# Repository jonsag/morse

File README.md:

# morse

Morse decoding and training gadgets

## Sections

This project will (probably) consist of two parts:  

* A CW paddle keyer  
* A morse decoder  

I have no real intention with this, other than that I think it could be fun testing these things out.  

### Keyer

A keyer based on the [nanoKeyer](https://nanokeyer.wordpress.com/) by Oscar, DJ0MY.  
NanoKeyer is built on the [K3NG Arduino CW Keyer](https://github.com/k3ng/k3ng_cw_keyer) open source project by [Anthony Good](https://github.com/k3ng).  
More documentation can be found at [github](https://github.com/ra0sms/nanokeyer).  

There's also the keyer, [Iambic Keyer Using Microcontroller](https://www.instructables.com/Iambic-Keyer-Using-Microcontroller/) by [fredlam](https://www.instructables.com/member/fredlam/).  
This uses the [PIC12F675](https://www.microchip.com/en-us/product/pic12f675), and perhaps I will delve into this approach later on, but for now I will stick to Oscar's design.  

### Decoder

A decoder based on [Morse Code Iambic Trainer and Decoder](https://www.instructables.com/Morse-Code-Iambic-Trainer-and-Decoder/) by [scd](https://www.instructables.com/member/scd/).  

## nanoKeyer build

If you don't want to print the entire casing, Oscar recommend these parts from [reichelt](https://www.reichelt.com)

* [KOH-0100, Profile housing half-shell, 100 x 6.73 mm, individually shrink-w](https://www.reichelt.com/se/en/shop/product/profile_housing_half-shell_100_x_6_73_mm_individually_shrink-w-58238?country=se&CCTYPE=private&LANGUAGE=en)  
* [KOH-4100, Profile housing half-shell, 100 x 32.1 mm, individually shrink-w](https://www.reichelt.com/se/en/shop/product/profile_housing_half-shell_100_x_32_1_mm_individually_shrink-w-58241)  
* [DPL 1-2, Cover set for half-shell profiles, KOH 1 + 2 packaged sets, 105](https://www.reichelt.com/se/en/shop/product/cover_set_for_half-shell_profiles_koh_1_2_packaged_sets_105-58257)  
* KNOPF 17-6 A, which is an aluminium knob for the potentiometer, but I couldn't find that at reichelt.  

If you instead want to print the faceplates fitting the casing above, there are stl's for [download at thingiverse](https://www.thingiverse.com/thing:4552149), designed by [Kaan, DL8GE](https://www.thingiverse.com/DL8GE).  

## Decoder build

Print the [casing found at thingiverse](https://www.thingiverse.com/thing:4875668).  

## Need a key?

The excellent twin paddle CW key by [EA7HVO](https://www.thingiverse.com/EA7HVO) can be downloaded from [thingiverse](https://www.thingiverse.com/thing:4586197).  4

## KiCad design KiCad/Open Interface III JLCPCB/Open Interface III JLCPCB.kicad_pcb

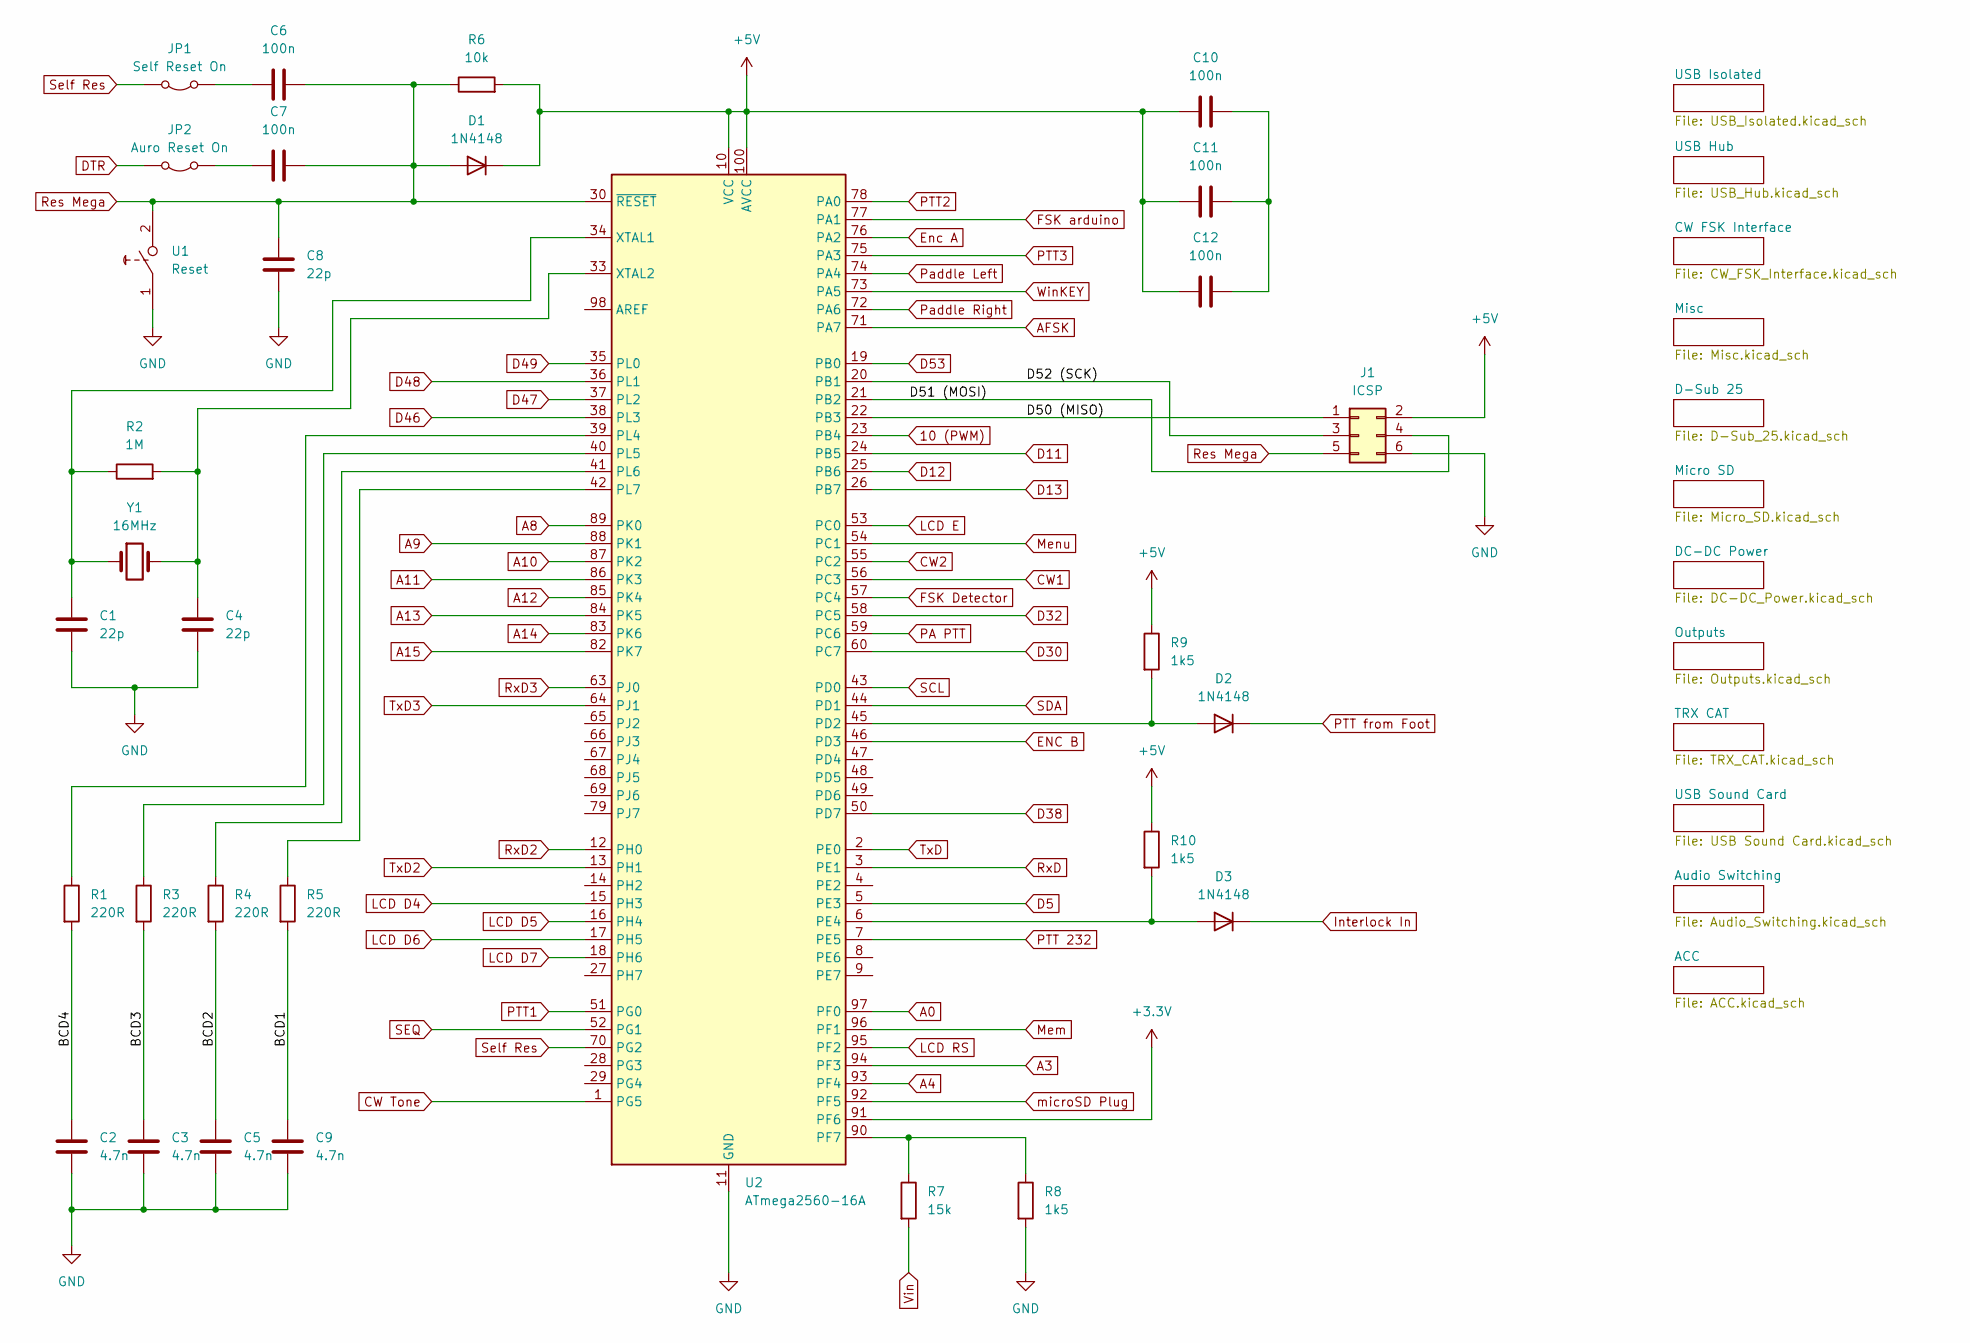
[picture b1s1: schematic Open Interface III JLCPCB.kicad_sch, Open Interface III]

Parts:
C1, C4, C8: 22p; C_0201_0603Metric; MPN C1653
C2, C3, C5, C9: 4.7n; C_0201_0603Metric; MPN C1621
C6, C7, C10, C11, C12: 100n; C_0201_0603Metric; MPN C1590
D1, D2, D3: 1N4148; D_SOD-523
J1: ICSP; 2x3_ISP_header
JP1: Self Reset On; PinHeader_1x02_P2.54mm_Vertical
JP2: Auro Reset On; PinHeader_1x02_P2.54mm_Vertical
R1, R3, R4, R5: 220R; R_0201_0603Metric; MPN C1226
R2: 1M; R_0201_0603Metric; MPN C22935
R6: 10k; R_0201_0603Metric; MPN C15401
R7: 15k; R_0201_0603Metric; MPN C22809
R8, R9, R10: 1k5; R_0201_0603Metric; MPN C22843
U1: Reset; 2-pin JST Switch
U2: ATmega2560-16A; TQFP-100_14x14mm_P0.5mm; MPN C22460
Y1: 16MHz; Crystal_SMD_HC49-SD; MPN C5346052

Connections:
10 (PWM): U2.23 (PB4); also elsewhere on the board
+3.3V: U2.91 (PF6); also elsewhere on the board
+5V: C10.1, C11.1, C12.1, D1.1 (K), J1.2, R6.2, R9.1, R10.1, U2.10 (VCC), U2.31 (VCC), U2.61 (VCC), U2.80 (VCC), U2.100 (AVCC); also elsewhere on the board
/BCD1: C9.1, R5.2
/BCD2: C5.1, R4.2
/BCD3: C3.1, R3.2
/BCD4: C2.1, R1.2
/D50 (MISO): J1.1, U2.22 (PB3)
/D51 (MOSI): J1.4, U2.21 (PB2)
/D52 (SCK): J1.3, U2.20 (PB1)
A0: U2.97 (PF0)
A3: U2.94 (PF3); also elsewhere on the board
A4: U2.93 (PF4); also elsewhere on the board
A8: U2.89 (PK0); also elsewhere on the board
A9: U2.88 (PK1); also elsewhere on the board
A10: U2.87 (PK2)
A11: U2.86 (PK3); also elsewhere on the board
A12: U2.85 (PK4)
A13: U2.84 (PK5)
A14: U2.83 (PK6)
A15: U2.82 (PK7)
AFSK: U2.71 (PA7); also elsewhere on the board
AGNDC: C1.2, C2.2, C3.2, C4.2, C5.2, C8.2, C9.2, J1.6, R8.2, U1.1 (Com), U2.11 (GND), U2.32 (GND), U2.62 (GND), U2.81 (GND), U2.99 (GND); also elsewhere on the board
CW1: U2.56 (PC3); also elsewhere on the board
CW2: U2.55 (PC2); also elsewhere on the board
CW Tone: U2.1 (PG5)
D5: U2.5 (PE3); also elsewhere on the board
D11: U2.24 (PB5); also elsewhere on the board
D12: U2.25 (PB6); also elsewhere on the board
D13: U2.26 (PB7); also elsewhere on the board
D30: U2.60 (PC7); also elsewhere on the board
D32: U2.58 (PC5); also elsewhere on the board
D38: U2.50 (PD7); also elsewhere on the board
D46: U2.38 (PL3); also elsewhere on the board
D47: U2.37 (PL2); also elsewhere on the board
D48: U2.36 (PL1)
D49: U2.35 (PL0)
D53: U2.19 (PB0); also elsewhere on the board
DTR: JP2.2 (B); also elsewhere on the board
ENC B: U2.46 (PD3)
Enc A: U2.76 (PA2); also elsewhere on the board
FSK Detector: U2.57 (PC4)
FSK arduino: U2.77 (PA1)
Interlock In: D3.1 (K); also elsewhere on the board
LCD D4: U2.15 (PH3); also elsewhere on the board
LCD D5: U2.16 (PH4); also elsewhere on the board
LCD D6: U2.17 (PH5); also elsewhere on the board
LCD D7: U2.18 (PH6)
LCD E: U2.53 (PC0); also elsewhere on the board
LCD RS: U2.95 (PF2); also elsewhere on the board
Mem: U2.96 (PF1)
Menu: U2.54 (PC1); also elsewhere on the board
unnamed: C10.2, C11.2, C12.2
unnamed: D2.2 (A), R9.2, U2.45 (PD2)
unnamed: D3.2 (A), R10.2, U2.6 (PE4)
unnamed: C6.1, JP1.1 (A)
unnamed: C7.1, JP2.1 (A)
unnamed: R7.1, R8.1, U2.90 (PF7)
unnamed: R1.1, U2.39 (PL4)
unnamed: R3.1, U2.40 (PL5)
unnamed: R4.1, U2.41 (PL6)
unnamed: R5.1, U2.42 (PL7)
unnamed: C1.1, R2.1, U2.34 (XTAL1), Y1.1
unnamed: C4.1, R2.2, U2.33 (XTAL2), Y1.2
PA PTT: U2.59 (PC6); also elsewhere on the board
PTT1: U2.51 (PG0); also elsewhere on the board
PTT2: U2.78 (PA0); also elsewhere on the board
PTT3: U2.75 (PA3); also elsewhere on the board
PTT 232: U2.7 (PE5); also elsewhere on the board
PTT from Foot: D2.1 (K); also elsewhere on the board
Paddle Left: U2.74 (PA4); also elsewhere on the board
Paddle Right: U2.72 (PA6); also elsewhere on the board
Res Mega: C6.2, C7.2, C8.1, D1.2 (A), J1.5, R6.1, U1.2 (NO), U2.30 (~RESET)
RxD: U2.3 (PE1); also elsewhere on the board
RxD2: U2.12 (PH0); also elsewhere on the board
RxD3: U2.63 (PJ0); also elsewhere on the board
SCL: U2.43 (PD0); also elsewhere on the board
SDA: U2.44 (PD1); also elsewhere on the board
SEQ: U2.52 (PG1); also elsewhere on the board
Self Res: JP1.2 (B), U2.70 (PG2)
TxD: U2.2 (PE0); also elsewhere on the board
TxD2: U2.13 (PH1); also elsewhere on the board
TxD3: U2.64 (PJ1); also elsewhere on the board
Vin: R7.2; also elsewhere on the board
WinKEY: U2.73 (PA5); also elsewhere on the board
microSD Plug: U2.92 (PF5); also elsewhere on the board

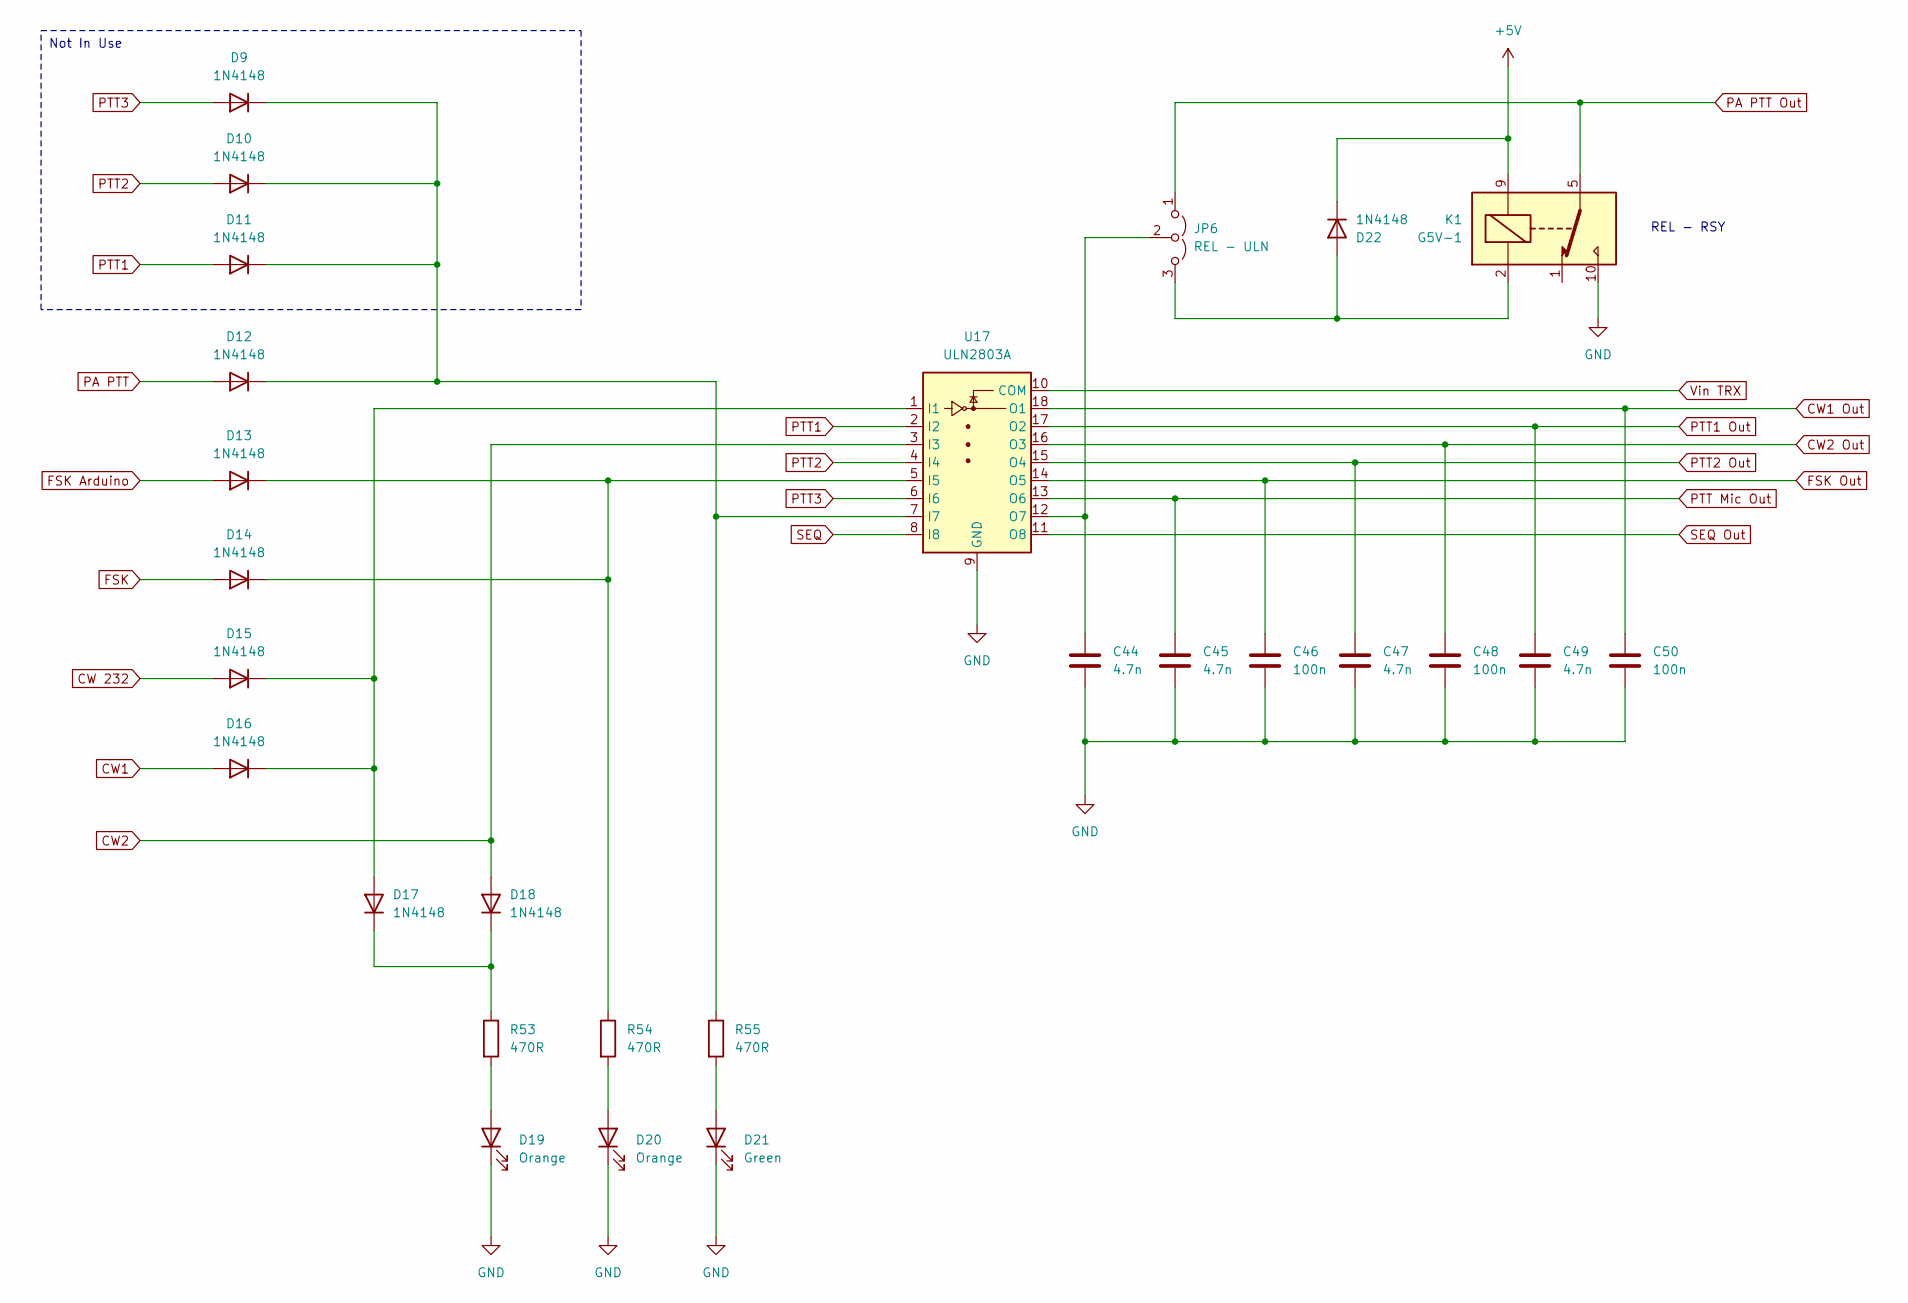
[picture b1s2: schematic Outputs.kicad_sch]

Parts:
C44, C45, C47, C49: 4.7n; C_0201_0603Metric; MPN C1621
C46, C48, C50: 100n; C_0201_0603Metric; MPN C1590
D9, D10, D11, D12, D13, D14, D15, D16, D17, D18, D22: 1N4148; D_SOD-523
D19, D20: Orange; 2-pin JST LED
D21: Green; 2-pin JST LED
JP6: REL - ULN; Jumper_1x03_P2.54mm_large
K1: G5V-1; Relay_SPDT_Omron_G5V-1
R53, R54, R55: 470R; R_0201_0603Metric; MPN C23179
U17: ULN2803A; SOIC-18W_7.5x11.6mm_P1.27mm; MPN C181731

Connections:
+5V: D22.1 (K), K1.9; also elsewhere on the board
AGNDC: C44.2, C45.2, C46.2, C47.2, C48.2, C49.2, C50.2, D19.1 (K), D20.1 (K), D21.1 (K), K1.10, U17.9 (GND); also elsewhere on the board
CW1: D16.2 (A); also elsewhere on the board
CW1 Out: C50.1, U17.18 (O1); also elsewhere on the board
CW2: D18.2 (A), U17.3 (I3); also elsewhere on the board
CW2 Out: C48.1, U17.16 (O3); also elsewhere on the board
CW 232: D15.2 (A); also elsewhere on the board
FSK: D14.2 (A); also elsewhere on the board
FSK Arduino: D13.2 (A)
FSK Out: C46.1, U17.14 (O5); also elsewhere on the board
unnamed: D9.1 (K), D10.1 (K), D11.1 (K), D12.1 (K), R55.1, U17.7 (I7)
unnamed: D13.1 (K), D14.1 (K), R54.1, U17.5 (I5)
unnamed: D15.1 (K), D16.1 (K), D17.2 (A), U17.1 (I1)
unnamed: D17.1 (K), D18.1 (K), R53.1
unnamed: D19.2 (A), R53.2
unnamed: D20.2 (A), R54.2
unnamed: D21.2 (A), R55.2
unnamed: D22.2 (A), JP6.3 (B), K1.2
unnamed: C44.1, JP6.2 (C), U17.12 (O7)
PA PTT: D12.2 (A); also elsewhere on the board
PA PTT Out: JP6.1 (A), K1.5, K1.6; also elsewhere on the board
PTT1: D11.2 (A), U17.2 (I2); also elsewhere on the board
PTT1 Out: C49.1, U17.17 (O2); also elsewhere on the board
PTT2: D10.2 (A), U17.4 (I4); also elsewhere on the board
PTT2 Out: C47.1, U17.15 (O4); also elsewhere on the board
PTT3: D9.2 (A), U17.6 (I6); also elsewhere on the board
PTT Mic Out: C45.1, U17.13 (O6); also elsewhere on the board
SEQ: U17.8 (I8); also elsewhere on the board
SEQ Out: U17.11 (O8); also elsewhere on the board
Vin TRX: U17.10 (COM); also elsewhere on the board

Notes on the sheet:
Not In Use
REL - RSY

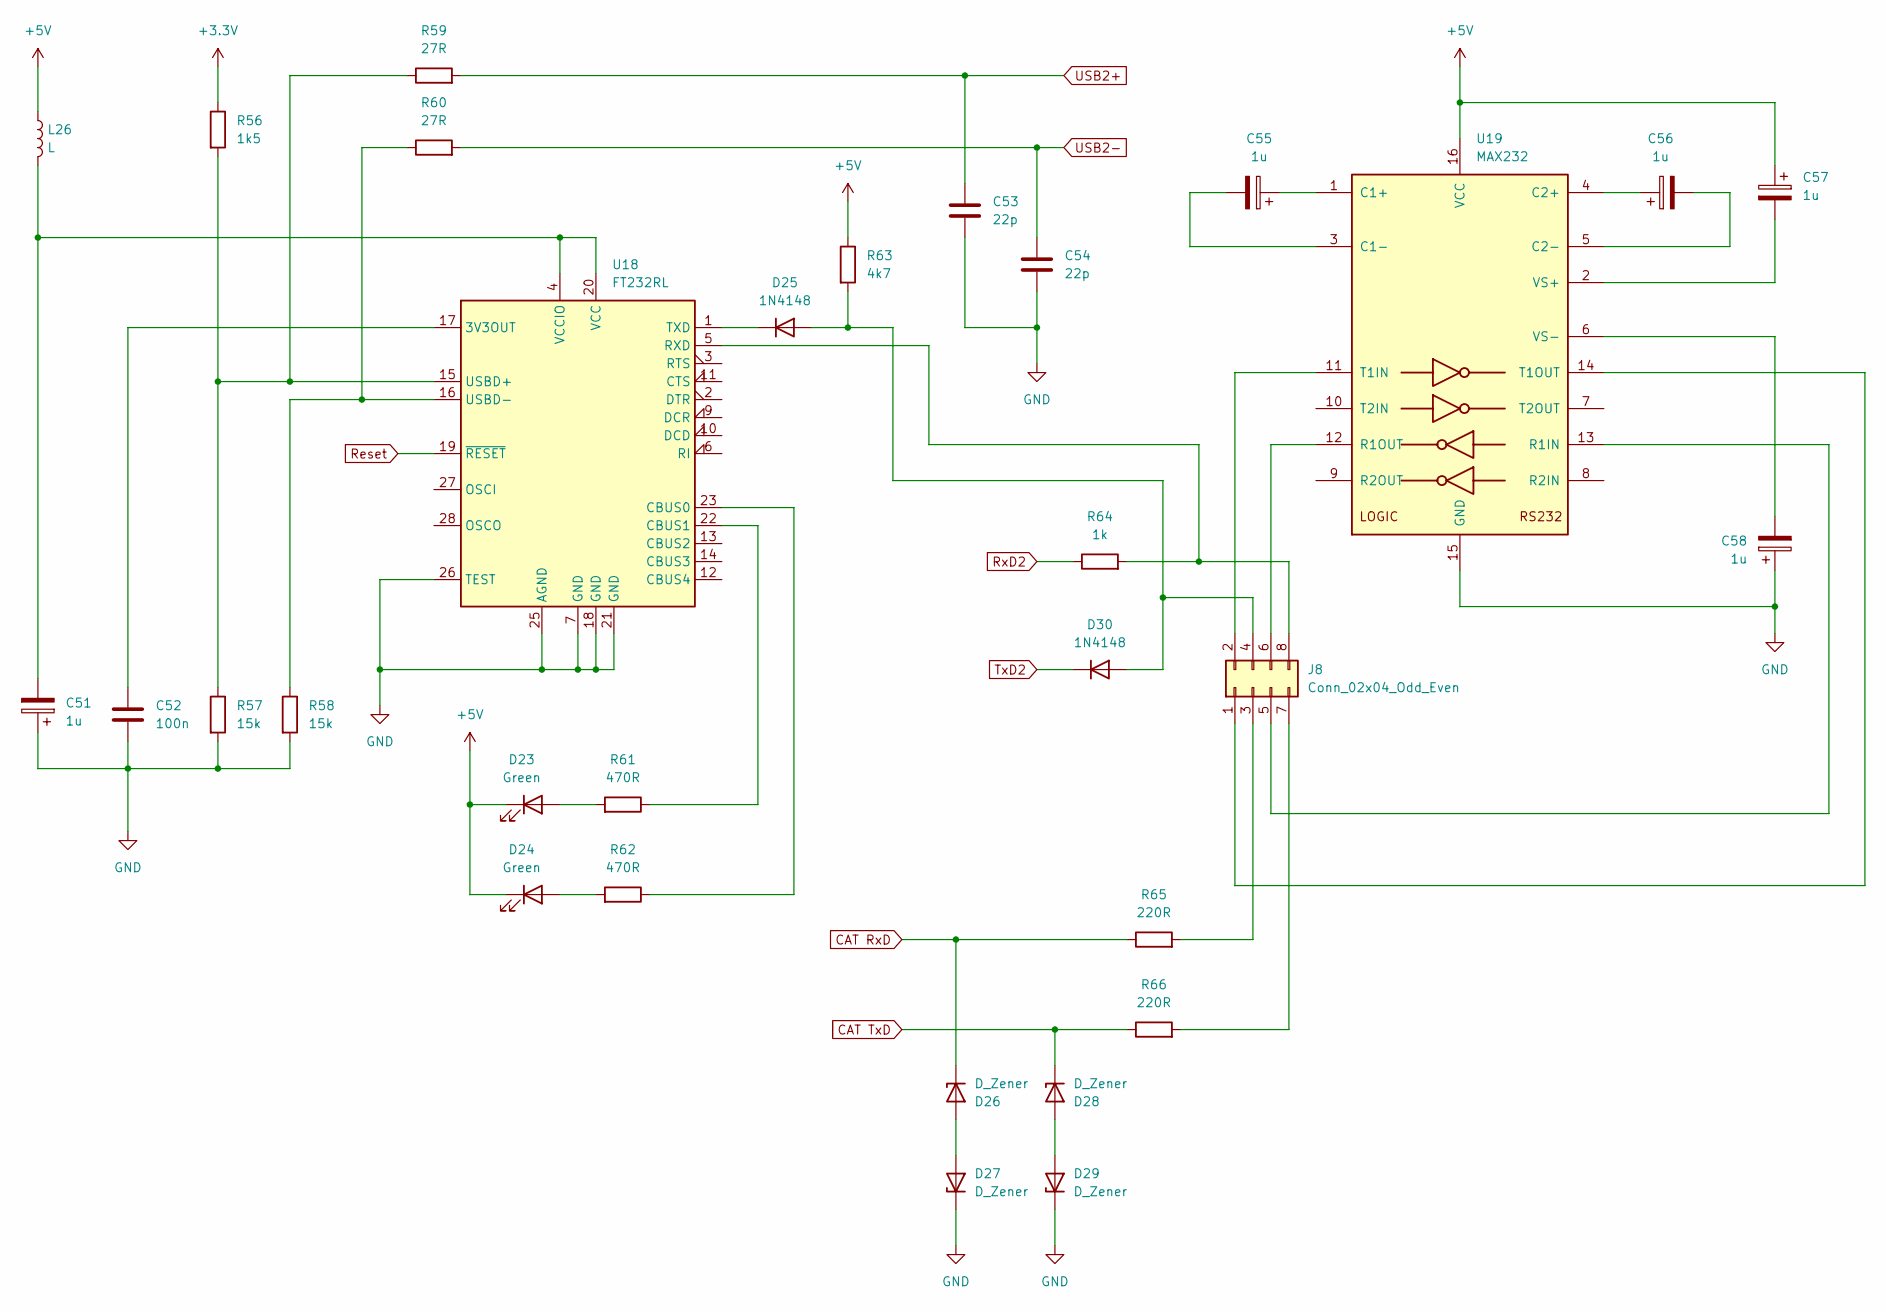
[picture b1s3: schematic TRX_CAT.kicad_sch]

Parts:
C51, C55, C56, C57, C58: 1u; CP_Elec_4x5.4; MPN C3348
C52: 100n; C_0201_0603Metric; MPN C1590
C53, C54: 22p; C_0201_0603Metric; MPN C1653
D23, D24: Green; 2-pin JST LED
D25, D30: 1N4148; D_SOD-523
D26, D27, D28, D29: D_Zener; SOT-23_Handsoldering
J8: Conn_02x04_Odd_Even; PinHeader_2x04_P2.54mm_Vertical
L26: L; L_1206_3216Metric_Pad1.22x1.90mm_HandSolder
R56: 1k5; R_0201_0603Metric; MPN C22843
R57, R58: 15k; R_0201_0603Metric; MPN C22809
R59, R60: 27R; R_0201_0603Metric; MPN C25190
R61, R62: 470R; R_0201_0603Metric; MPN C23179
R63: 4k7; R_0201_0603Metric; MPN C23162
R64: 1k; R_0201_0603Metric; MPN C14676
R65, R66: 220R; R_0201_0603Metric; MPN C1226
U18: FT232RL; SSOP-28_5.3x10.2mm_P0.65mm
U19: MAX232; SOP-16_3.9x9.9mm_P1.27mm; MPN C5342103

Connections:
+3.3V: R56.1; also elsewhere on the board
+5V: C57.1, D23.1 (K), D24.1 (K), L26.1, R63.1, U19.16 (VCC); also elsewhere on the board
AGNDC: C51.1, C52.2, C53.2, C54.2, C58.1, D27.1 (K), D29.1 (K), R57.2, R58.2, U18.7 (GND), U18.18 (GND), U18.21 (GND), U18.25 (AGND), U18.26 (TEST), U19.15 (GND); also elsewhere on the board
CAT RxD: D26.1 (K), R65.1; also elsewhere on the board
CAT TxD: D28.1 (K), R66.1; also elsewhere on the board
DTR: U18.19 (~RESET); also elsewhere on the board
unnamed: D23.2 (A), R61.2
unnamed: D24.2 (A), R62.2
unnamed: D25.2 (A), D30.2 (A), J8.4, R63.2
unnamed: D25.1 (K), U18.1 (TXD)
unnamed: D26.2 (A), D27.2 (A)
unnamed: D28.2 (A), D29.2 (A)
unnamed: J8.1, U19.14 (T1OUT)
unnamed: J8.2, U19.11 (T1IN)
unnamed: J8.3, R65.2
unnamed: J8.5, U19.13 (R1IN)
unnamed: J8.6, U19.12 (R1OUT)
unnamed: J8.7, R66.2
unnamed: J8.8, R64.2, U18.5 (RXD)
unnamed: C52.1, U18.17 (3V3OUT)
unnamed: R62.1, U18.23 (CBUS0)
unnamed: R61.1, U18.22 (CBUS1)
unnamed: R56.2, R57.1, R59.1, U18.15 (USBD+)
unnamed: R58.1, R60.1, U18.16 (USBD-)
unnamed: C51.2, L26.2, U18.4 (VCCIO), U18.20 (VCC)
unnamed: C55.1, U19.1 (C1+)
unnamed: C55.2, U19.3 (C1-)
unnamed: C56.1, U19.4 (C2+)
unnamed: C56.2, U19.5 (C2-)
unnamed: C57.2, U19.2 (VS+)
unnamed: C58.2, U19.6 (VS-)
RxD2: R64.1; also elsewhere on the board
TxD2: D30.1 (K); also elsewhere on the board
USB2+: C53.1, R59.2; also elsewhere on the board
USB2-: C54.1, R60.2; also elsewhere on the board

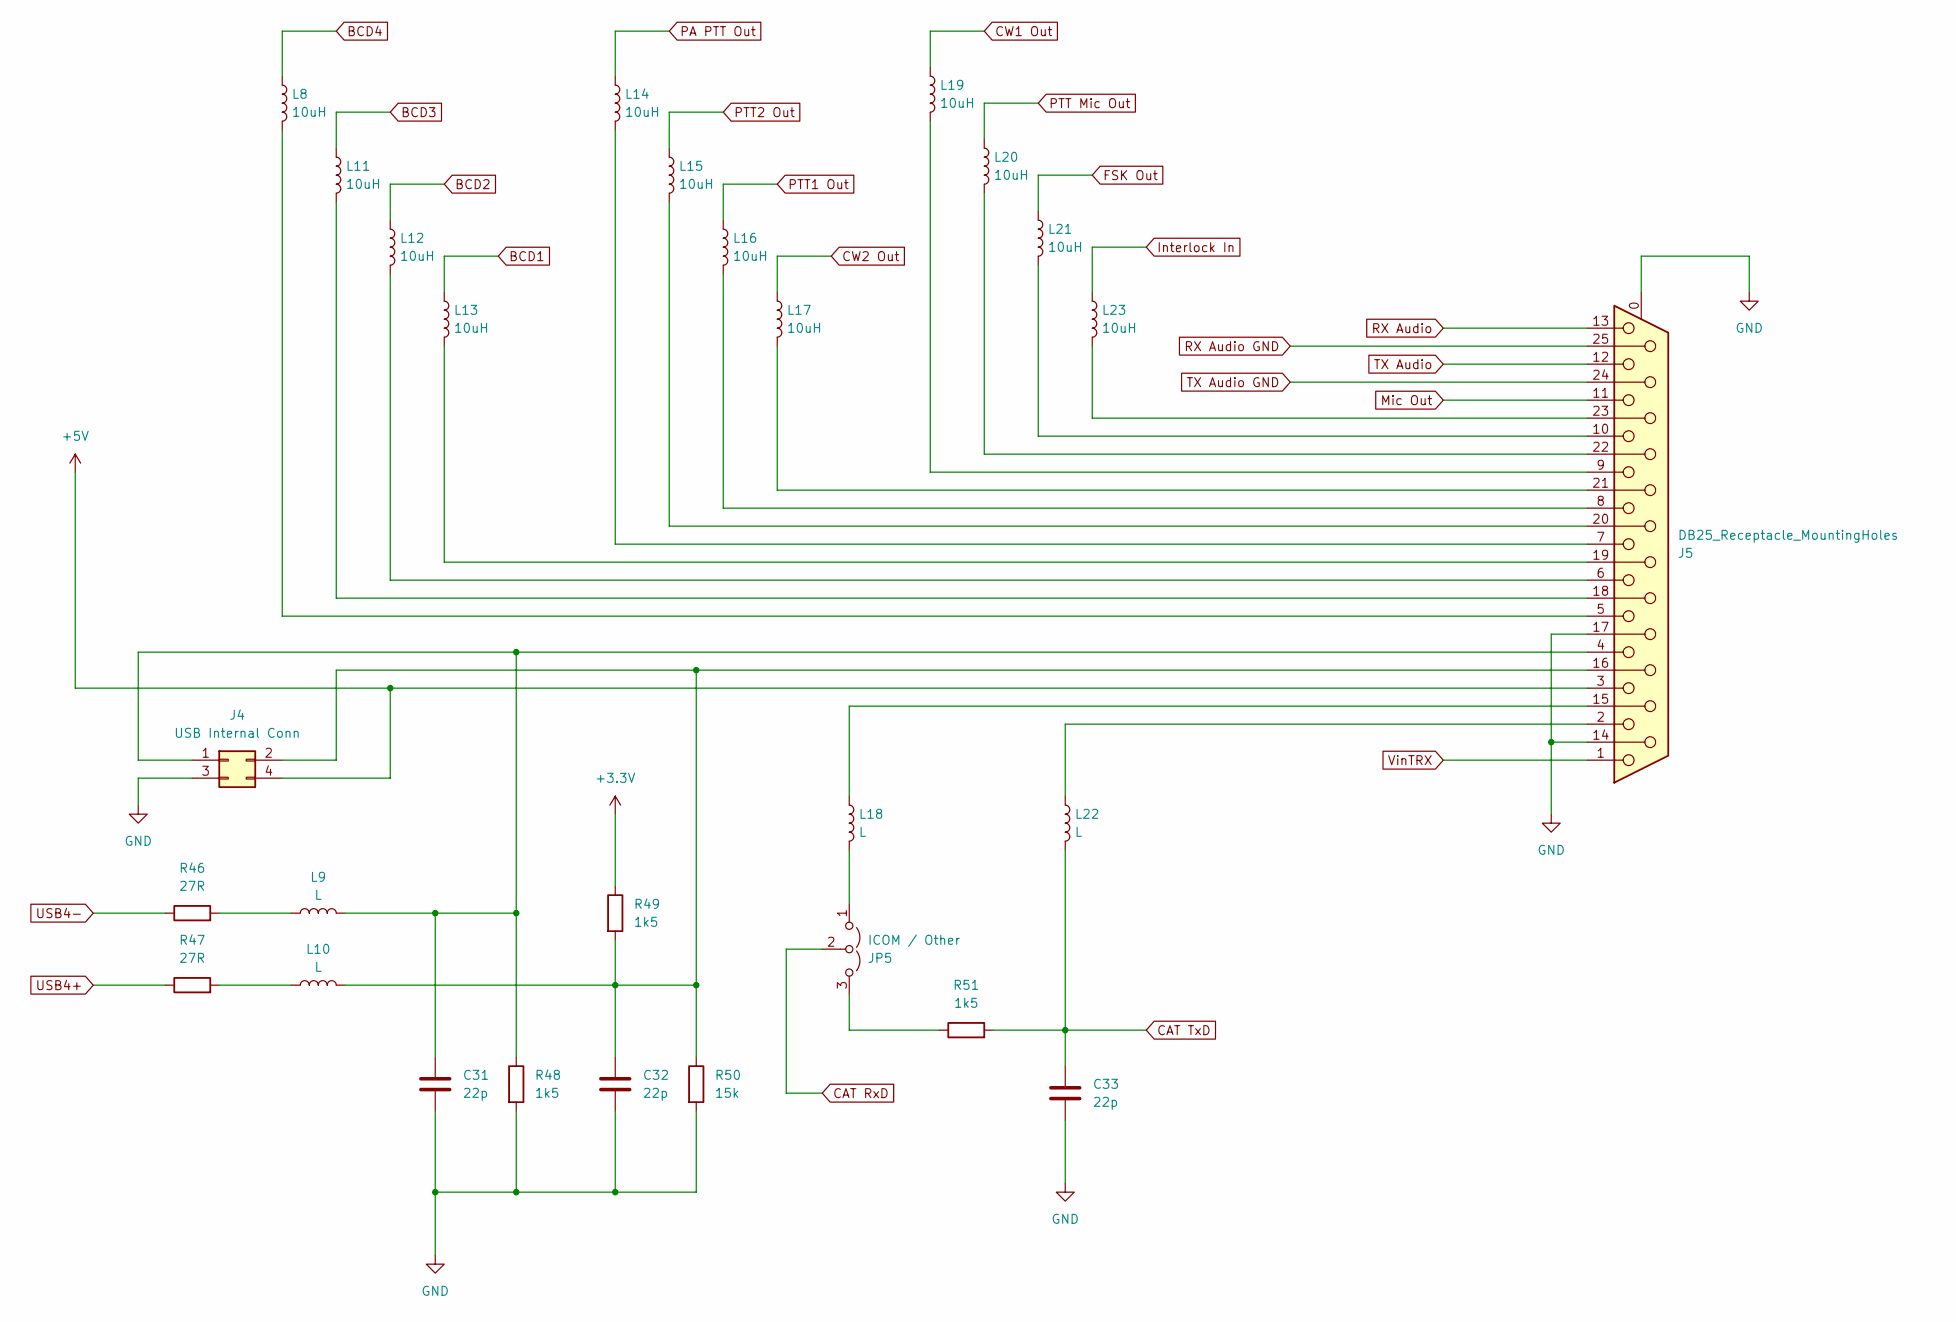
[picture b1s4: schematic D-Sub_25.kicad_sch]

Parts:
C31, C32, C33: 22p; C_0201_0603Metric; MPN C1653
J4: USB Internal Conn; PinHeader_2x02_P2.54mm_Vertical
J5: DB25_Receptacle_MountingHoles; DSUB-25_Female_Horizontal_P2.77x2.84mm_EdgePinOffset4.94mm_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
JP5: ICOM / Other; Jumper_1x03_P2.54mm_large
L8, L11, L12, L13, L14, L15, L16, L17, L19, L20, L21, L23: 10uH; L_0201_0603Metric; MPN C1035
L9, L10, L18, L22: L; L_1206_3216Metric_Pad1.22x1.90mm_HandSolder
R46, R47: 27R; R_0201_0603Metric; MPN C25190
R48, R49, R51: 1k5; R_0201_0603Metric; MPN C22843
R50: 15k; R_0201_0603Metric; MPN C22809

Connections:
+3.3V: R49.1; also elsewhere on the board
+5V: J4.4, J5.3; also elsewhere on the board
AGNDC: C31.2, C32.2, C33.2, J4.3, J5.0 (PAD), J5.14, J5.17, R48.2, R50.2; also elsewhere on the board
BCD1: L13.1
BCD2: L12.1
BCD3: L11.1
BCD4: L8.1
CAT RxD: JP5.2 (C); also elsewhere on the board
CAT TxD: C33.1, L22.2, R51.2; also elsewhere on the board
CW1 Out: L19.1; also elsewhere on the board
CW2 Out: L17.1; also elsewhere on the board
FSK Out: L21.1; also elsewhere on the board
Interlock In: L23.1; also elsewhere on the board
Mic Out: J5.11; also elsewhere on the board
unnamed: C31.1, J4.1, J5.4, L9.2, R48.1
unnamed: C32.1, J4.2, J5.16, L10.2, R49.2, R50.1
unnamed: J5.15, L18.1
unnamed: J5.18, L11.2
unnamed: J5.19, L13.2
unnamed: J5.20, L15.2
unnamed: J5.21, L17.2
unnamed: J5.22, L20.2
unnamed: J5.23, L23.2
unnamed: J5.2, L22.1
unnamed: J5.5, L8.2
unnamed: J5.6, L12.2
unnamed: J5.7, L14.2
unnamed: J5.8, L16.2
unnamed: J5.9, L19.2
unnamed: J5.10, L21.2
unnamed: JP5.1 (A), L18.2
unnamed: JP5.3 (B), R51.1
unnamed: L9.1, R46.2
unnamed: L10.1, R47.2
PA PTT Out: L14.1; also elsewhere on the board
PTT1 Out: L16.1; also elsewhere on the board
PTT2 Out: L15.1; also elsewhere on the board
PTT Mic Out: L20.1; also elsewhere on the board
RX Audio: J5.13
RX Audio GND: J5.25
TX Audio: J5.12
TX Audio GND: J5.24
USB4+: R47.1; also elsewhere on the board
USB4-: R46.1; also elsewhere on the board
VinTRX: J5.1

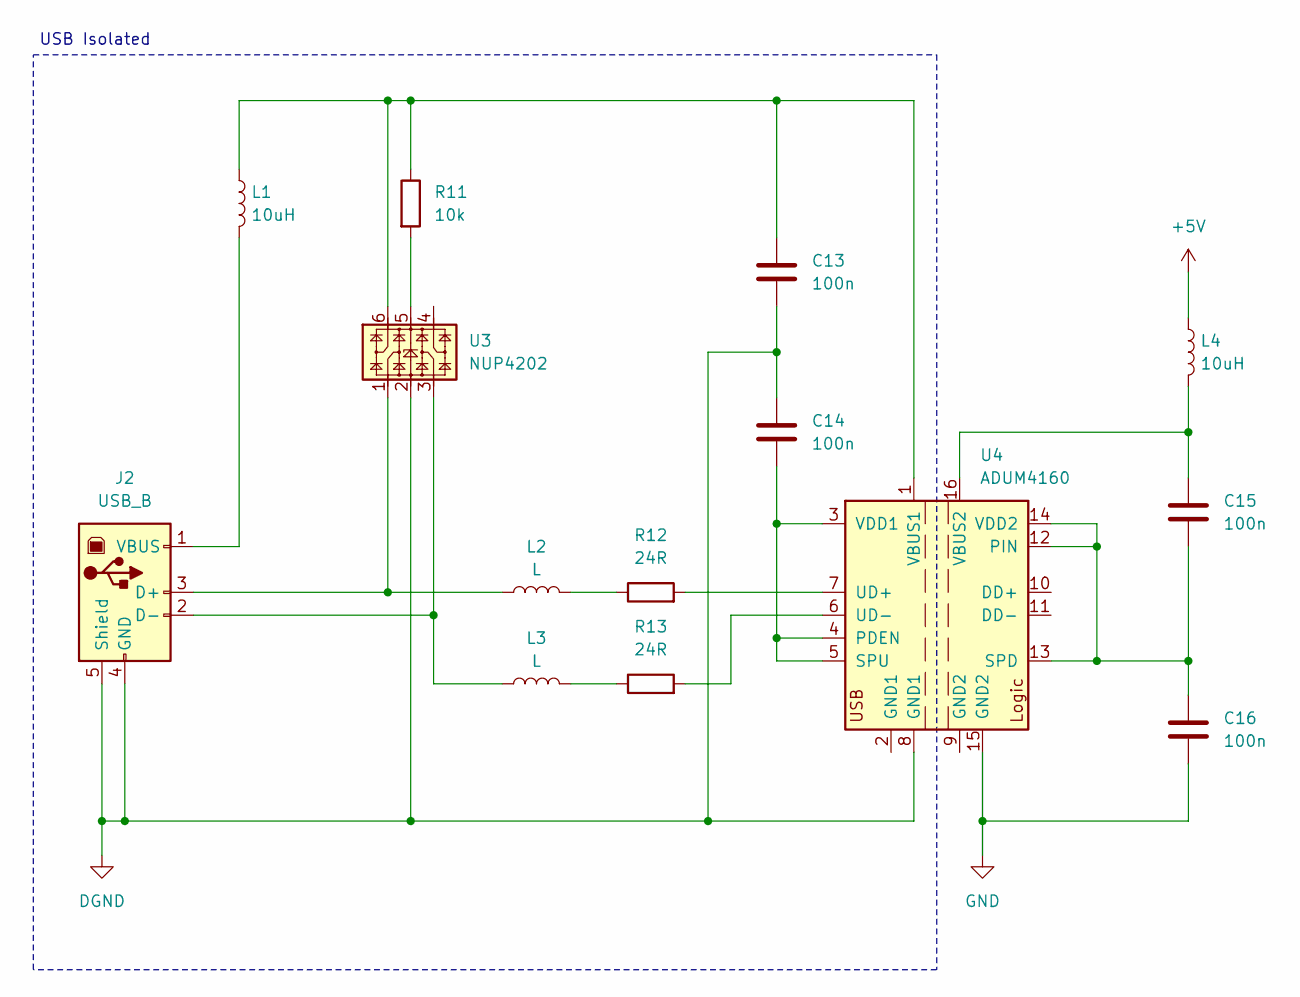
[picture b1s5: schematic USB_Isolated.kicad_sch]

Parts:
C13, C14, C15, C16: 100n; C_0201_0603Metric; MPN C1590
J2: USB_B; USB_B_OST_USB-B1HSxx_Horizontal
L1, L4: 10uH; L_0201_0603Metric; MPN C1035
L2, L3: L; L_1206_3216Metric_Pad1.22x1.90mm_HandSolder
R11: 10k; R_0201_0603Metric; MPN C15401
R12, R13: 24R; R_0201_0603Metric; MPN C4198
U3: NUP4202; SOT-363_SC-70-6
U4: ADUM4160; SOIC-16W_7.5x10.3mm_P1.27mm

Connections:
+5V: L4.1; also elsewhere on the board
AGNDC: C16.2, U4.15 (GND2); also elsewhere on the board
DGND: C13.2, C14.1, J2.4 (GND), J2.5 (Shield), U3.2, U4.8 (GND1)
unnamed: J2.3 (D+), L2.1, U3.1
unnamed: J2.2 (D-), L3.1, U3.3
unnamed: J2.1 (VBUS), L1.2
unnamed: L2.2, R12.1
unnamed: L3.2, R13.1
unnamed: R11.2, U3.5
unnamed: C14.2, U4.3 (VDD1), U4.4 (PDEN), U4.5 (SPU)
unnamed: C15.2, C16.1, U4.12 (PIN), U4.13 (SPD), U4.14 (VDD2)
unnamed: R12.2, U4.7 (UD+)
unnamed: R13.2, U4.6 (UD-)
unnamed: C13.1, L1.1, R11.1, U3.6, U4.1 (VBUS1)
unnamed: C15.1, L4.2, U4.16 (VBUS2)

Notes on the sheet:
USB Isolated

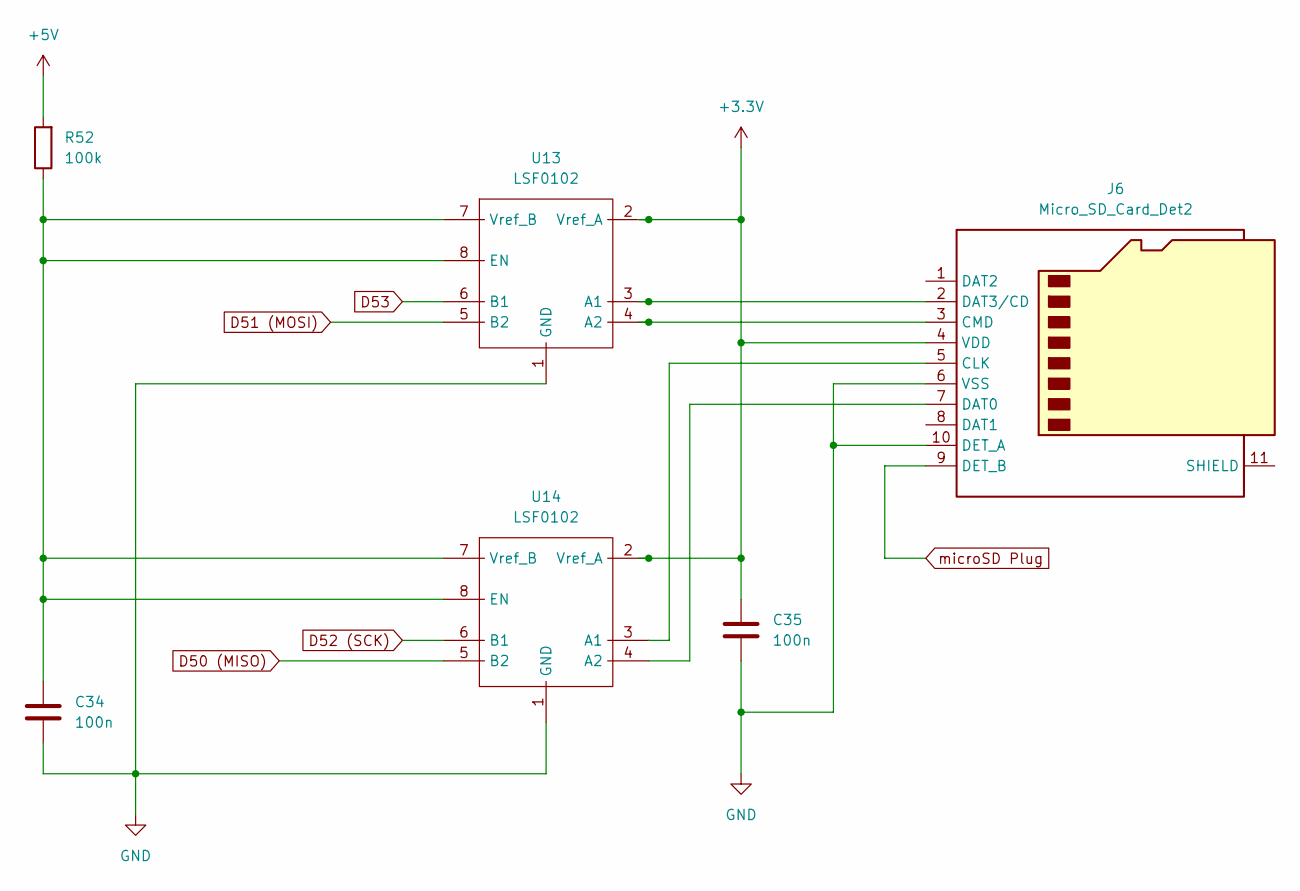
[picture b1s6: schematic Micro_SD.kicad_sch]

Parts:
C34, C35: 100n; C_0201_0603Metric; MPN C1590
J6: Micro_SD_Card_Det2; microSD_HC_Hirose_DM3AT-SF-PEJM5
R52: 100k; R_0201_0603Metric; MPN C14675
U13, U14: LSF0102; VSSOP-8_3x3mm_P0.65mm; MPN C4363955

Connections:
+3.3V: C35.1, J6.4 (VDD), U13.2 (Vref_A), U14.2 (Vref_A); also elsewhere on the board
+5V: R52.2; also elsewhere on the board
AGNDC: C34.2, C35.2, J6.6 (VSS), J6.10 (DET_A), U13.1 (GND), U14.1 (GND); also elsewhere on the board
D50 (MISO): U14.5 (B2); also elsewhere on the board
D51 (MOSI): U13.5 (B2); also elsewhere on the board
D52 (SCK): U14.6 (B1); also elsewhere on the board
D53: U13.6 (B1); also elsewhere on the board
unnamed: J6.5 (CLK), U14.3 (A1)
unnamed: J6.3 (CMD), U13.4 (A2)
unnamed: J6.7 (DAT0), U14.4 (A2)
unnamed: J6.2 (DAT3/CD), U13.3 (A1)
unnamed: C34.1, R52.1, U13.7 (Vref_B), U13.8 (EN), U14.7 (Vref_B), U14.8 (EN)
microSD Plug: J6.9 (DET_B); also elsewhere on the board
